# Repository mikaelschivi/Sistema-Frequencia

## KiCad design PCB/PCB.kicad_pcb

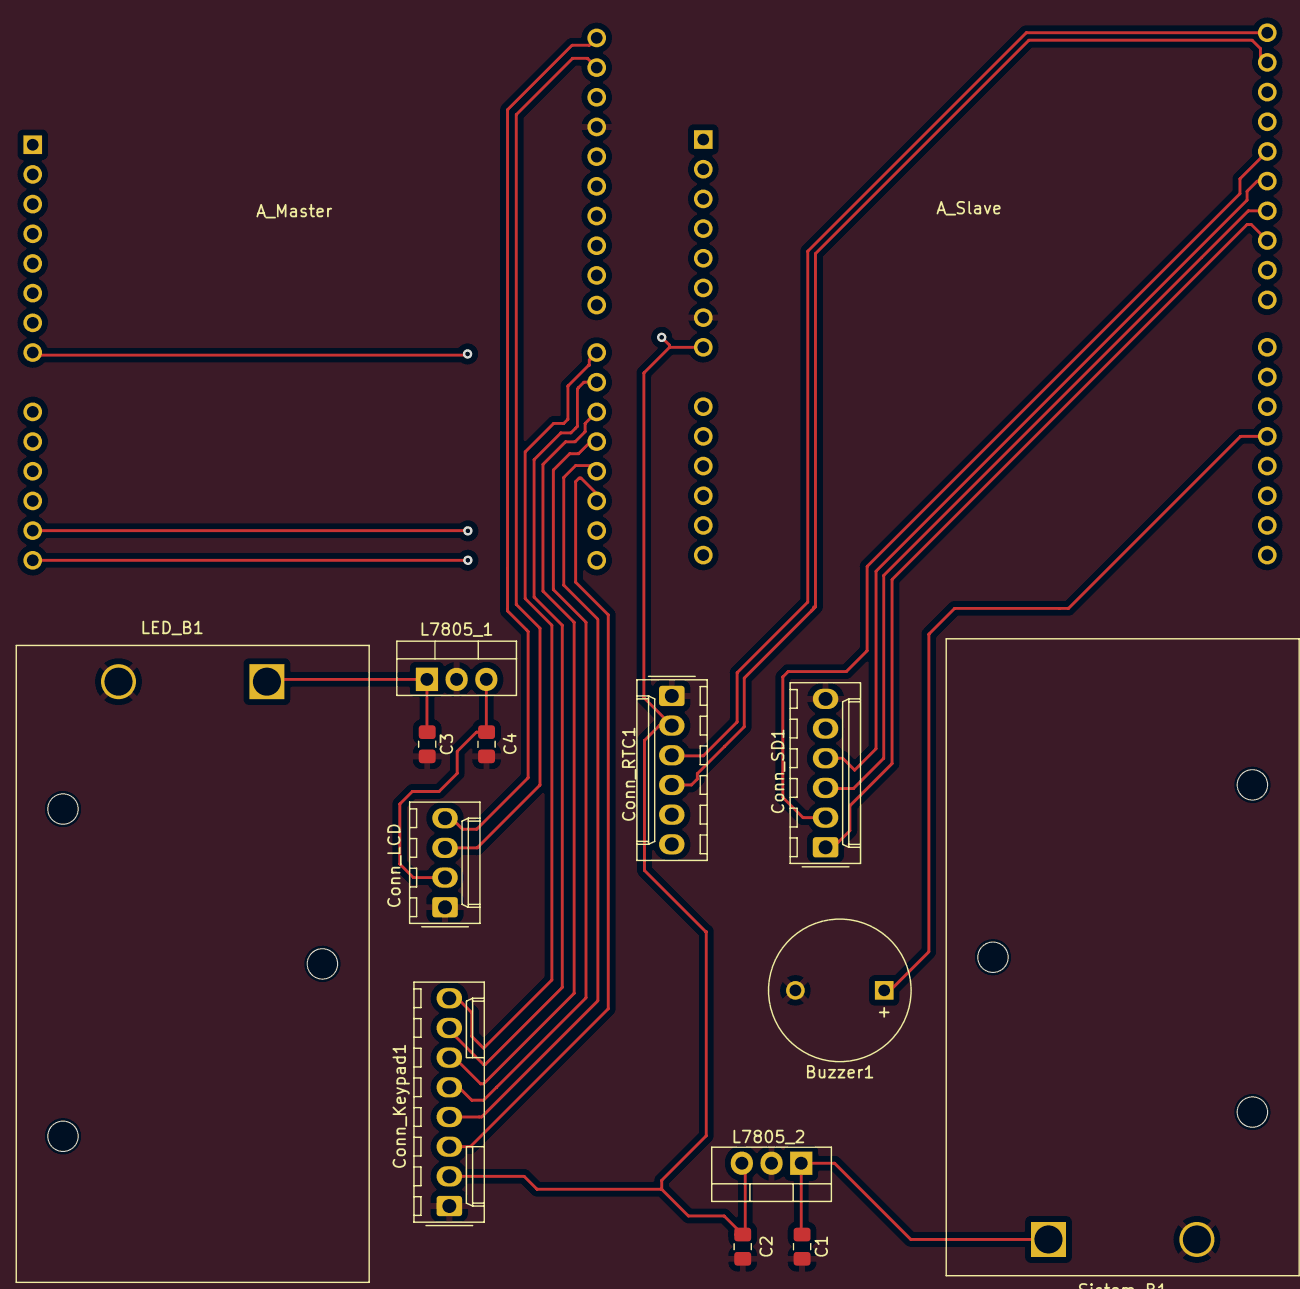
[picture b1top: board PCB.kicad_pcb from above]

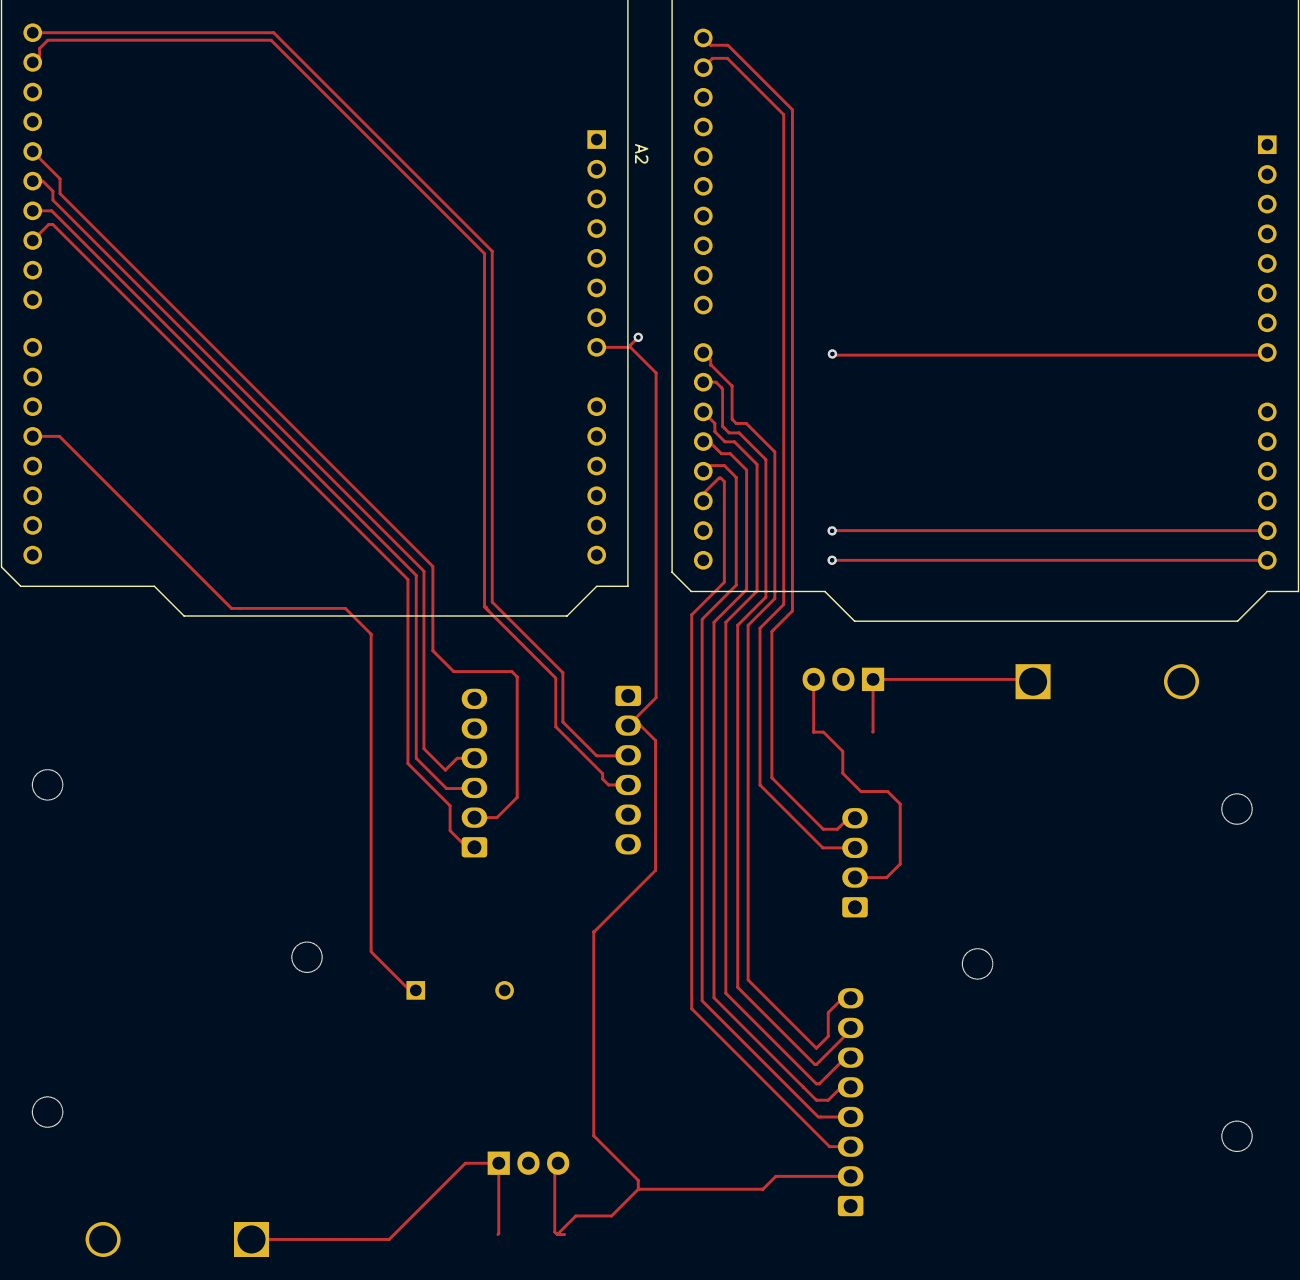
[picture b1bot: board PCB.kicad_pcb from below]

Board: 2 copper layers, 15 parts (2 on the bottom side), 21 nets.

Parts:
A1: Master; Arduino_UNO_R3
A2: Slave; Arduino_UNO_R3
Buzzer1: Buzzer; MagneticBuzzer_ProSignal_ABI-010-RC
C1, C3: 0.33uF; C_0805_2012Metric_Pad1.18x1.45mm_HandSolder
C2, C4: 0.01uF; C_0805_2012Metric_Pad1.18x1.45mm_HandSolder
Conn_Keypad1: Conn_Keypad; Molex_KK-254_AE-6410-08A_1x08_P2.54mm_Vertical
Conn_RTC1: Conn_RTC; Molex_KK-254_AE-6410-06A_1x06_P2.54mm_Vertical
Conn_SD1: Conn_RTC; Molex_KK-254_AE-6410-06A_1x06_P2.54mm_Vertical
J3: Conn_LCD; Molex_KK-254_AE-6410-04A_1x04_P2.54mm_Vertical
L7805_1, L7805_2: L7805; TO-220-3_Vertical
LED_B1: LCD battery; BatteryHolder_Eagle_12BH611-GR
Sistem_B1: Sistem battery; BatteryHolder_Eagle_12BH611-GR

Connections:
5V+_LCD: C4.2, J3.2, L7805_1.3 (OUT)
5V+_Sistem: A1.8 (VIN), A2.8 (VIN), C2.2, Conn_Keypad1.2, Conn_RTC1.2, Conn_SD1.5, L7805_2.3 (OUT)
9V+_LCD: C3.1, L7805_1.1 (IN), LED_B1.1 (+)
9V+_Sistem: C1.1, L7805_2.1 (IN), Sistem_B1.1 (+)
CS: A2.25 (D10), Conn_SD1.1
GNDREF: A1.29 (GND), A2.7 (GND), Buzzer1.2 (+), C1.2, C2.1, C3.2, C4.1, Conn_Keypad1.1, Conn_RTC1.1, Conn_SD1.6, J3.1, L7805_1.2 (GND), L7805_2.2 (GND), LED_B1.2 (-), Sistem_B1.2 (-)
MISO_SD: A2.27 (D12), Conn_SD1.4
MOSI_SD: A2.26 (D11), Conn_SD1.3
P2_keyPad: A1.17 (D2), Conn_Keypad1.3
P3_keyPad: A1.18 (D3), Conn_Keypad1.4
P4_keyPad: A1.19 (D4), Conn_Keypad1.5
P5_keyPad: A1.20 (D5), Conn_Keypad1.6
P6_keyPad: A1.21 (D6), Conn_Keypad1.7
P7_keyPad: A1.22 (D7), Conn_Keypad1.8
SCK: A2.28 (D13), Conn_SD1.2
SCL_LCD: A1.32 (SCL/A5), J3.4
SCL_MS: A1.14 (SCL/A5), A2.14 (SCL/A5)
SCL_RTC: A2.32 (SCL/A5), Conn_RTC1.3
SDA_LCD: A1.31 (SDA/A4), J3.3
SDA_MS: A1.13 (SDA/A4), A2.13 (SDA/A4)
SDA_RTC: A2.31 (SDA/A4), Conn_RTC1.4

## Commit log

2023-03-16 add pseudo-code
2023-04-13 Codigo pro Keypad
2023-04-22 novo codigo - integrando LCD+Keypad :)
2023-05-02 updated code for utilizing RTC module - Maintaining old code for backup
2023-05-02 moving files
2023-06-12 .
    .
2023-06-19 codigo certo :)
2023-06-26 limpando a casa
2023-06-26 add libs
2023-06-28 Master/Slave
2023-06-30 Master and Slave
2023-06-30 arrumadinha :)
2023-06-30 refatorada de levs
2023-07-04 Master/Slave mod
2023-11-26 envio PCB
2023-11-26 trilhas PCB
2023-12-10 caixaPCB
